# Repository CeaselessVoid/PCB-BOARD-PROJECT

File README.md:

# PCB-BOARD-PROJECT
Currently we still need to flesh out our design in terms of component choice, back up designs and the actual design.
Below is all the data we have currently(the requirements of the project) :
1. Operate up to 4 motors bidirectionally with the pins available to you (listed in the power pinout table). You will need to control 2x brushed DC motors which could each draw 200mA at the highest voltage of a 1S1P battery (the battery is further specified in the battery section).The other 2x motors are for the auxiliary connection and need to operate 500mA each.
2. Place an INA219 for monitoring the battery on the I2C Bus and configure it correctly with respect to the hardware (cannot have BOTH A0 AND A1 on GND)
3. Charge the battery from the 9V input pin (listed in the power pinout table).
4. Have two charging modes for a higher and lower charging current for the battery (200mA, and approximately 600mA ±100mA from the battery perspective.
5. Integrate USB C and get 9V out of the USB Host
6. Provide 2x External Load Switching at 1A each (High Side connected to your 5V)
7. Provide a 3V3 5% accuracy (300mA max) and 5V Out 5% accuracy (1.5A max)
8. Provide an ON/OFF switch. OFF state: battery draw <30uA. ON state: can provide your robot peak current of 2A. The switch needs to shut down 5V and 3V3.

So far we have locked in the components INA219 and possiblely the H-bridge. This will need to be deducted from our budget once we fin a suitable vendor.(As it stands we have $56.5 for the components).
Other points:
1. The board solution should be 82 x 60 (mm)
2. We cannot excede the budget
3. Deadline is the 28th of March (we should try to finalize well before this)
4. All components sourced from JLCPCB

Future things to add here: 
1. We need to add the schemetic and PCB design
2. Possible links to the datasheets we used for an easier time during report writing
3. Any computations we do(again mainly for reference)

https://cdn-shop.adafruit.com/datasheets/ina219.pdf - INA219

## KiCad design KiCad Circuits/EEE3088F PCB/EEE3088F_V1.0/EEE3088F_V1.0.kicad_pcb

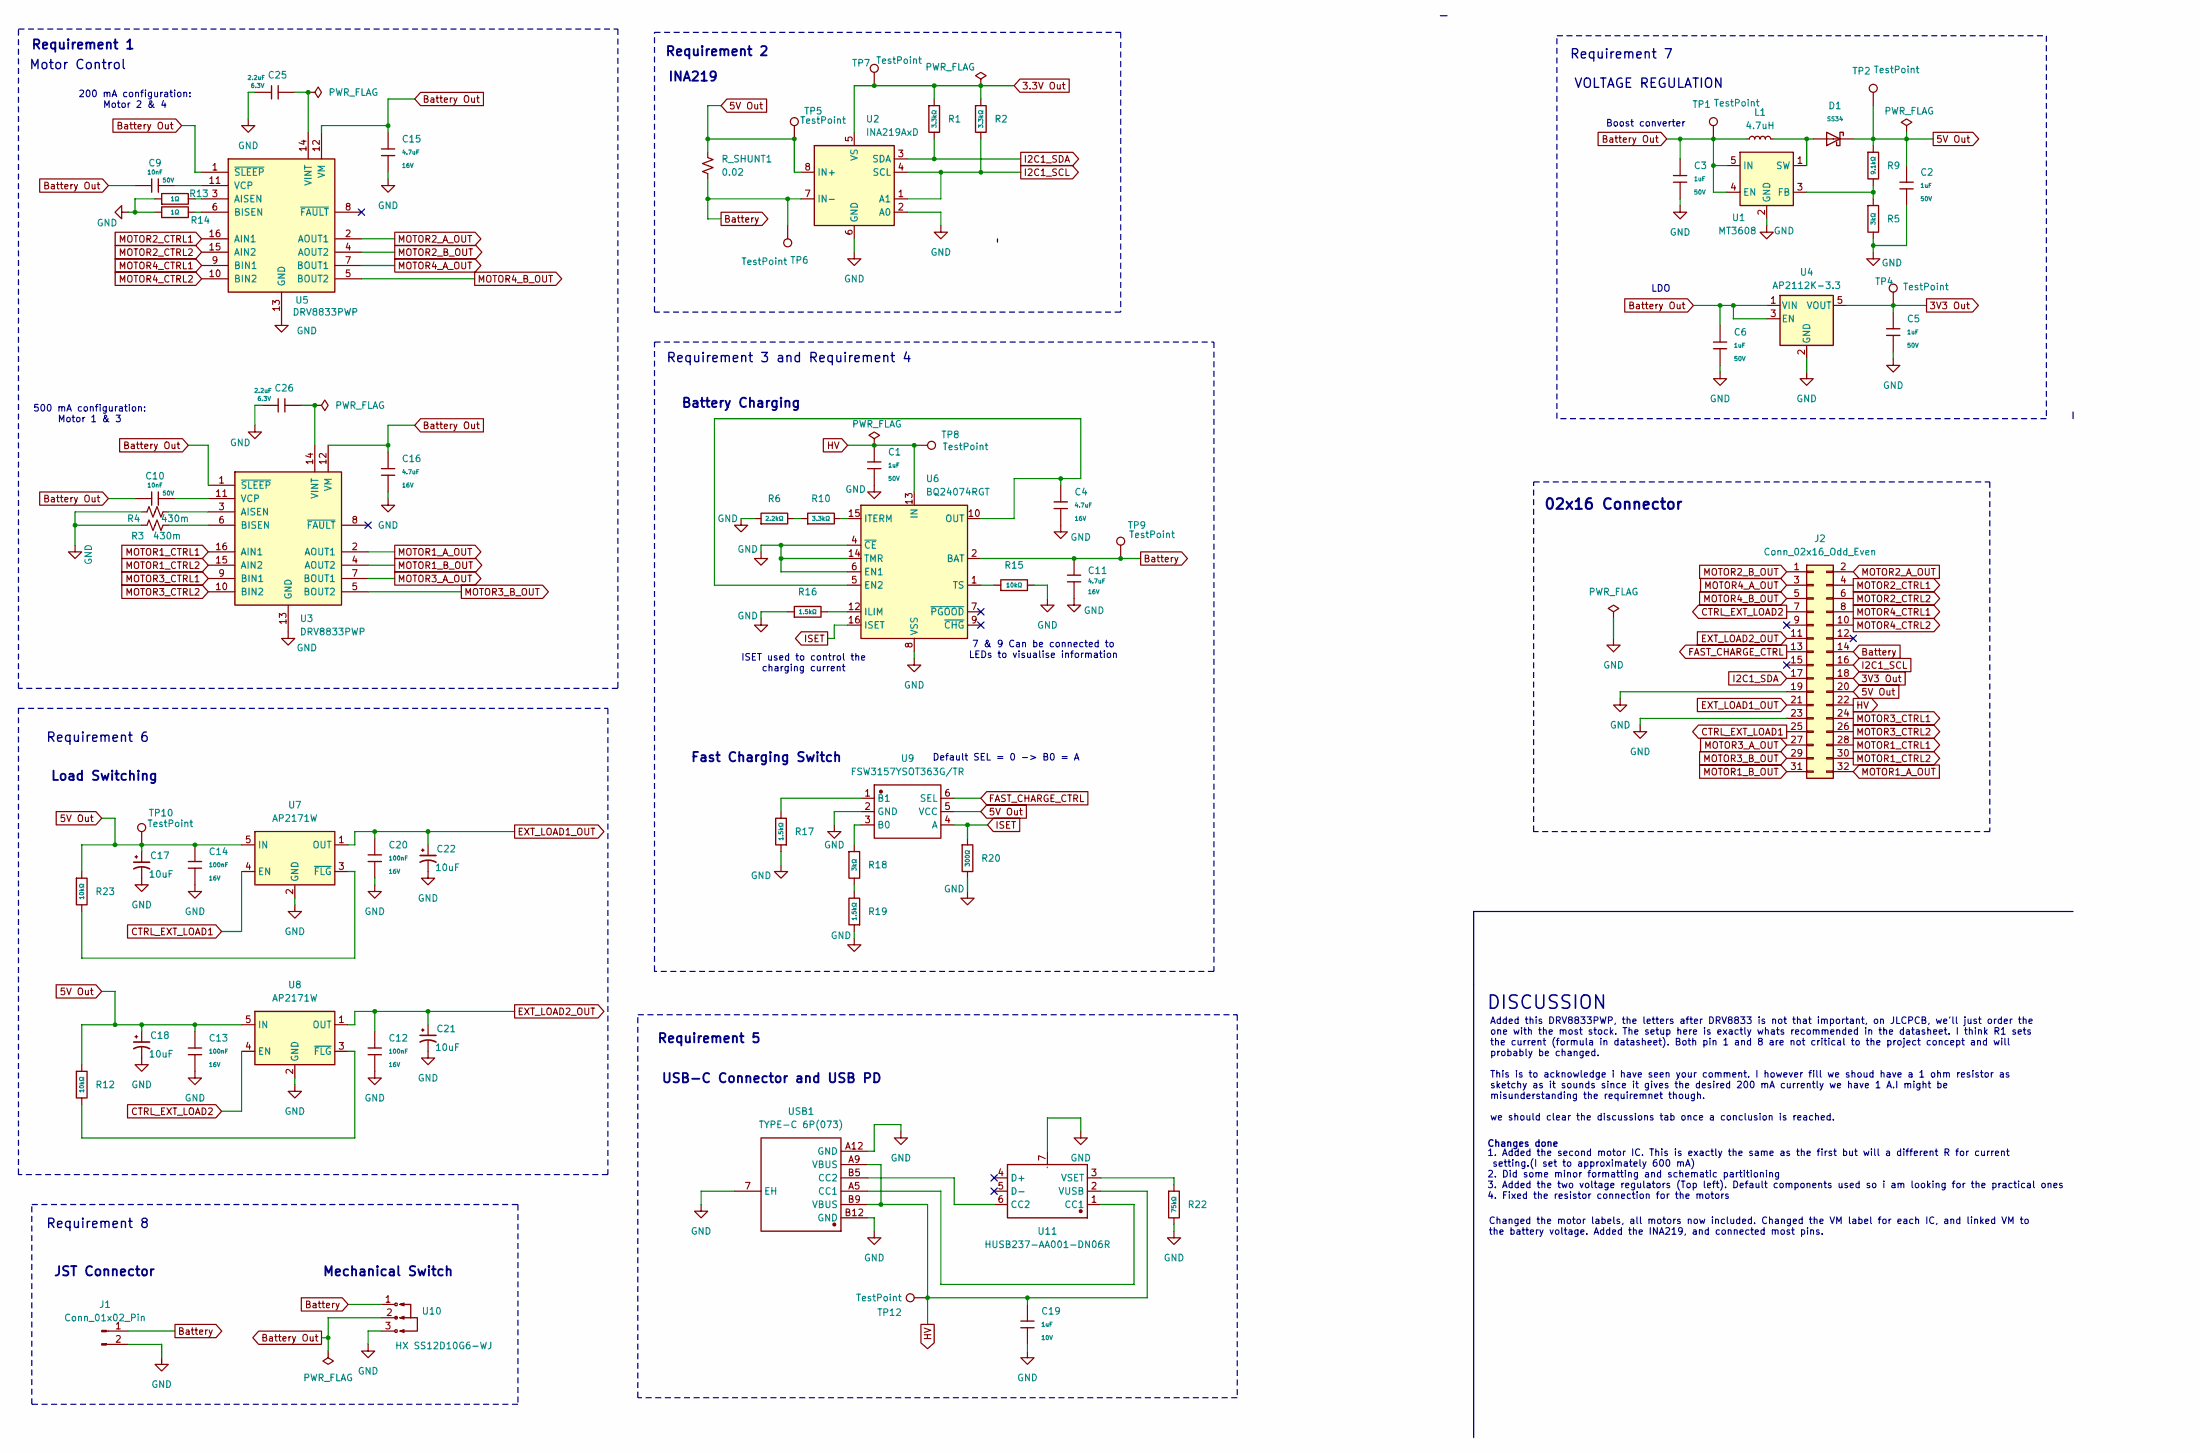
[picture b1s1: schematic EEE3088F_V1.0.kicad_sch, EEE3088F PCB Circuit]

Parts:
C1, C2, C3, C5, C6: 1uF; C_0603; Voltage Rated 50V; Tolerance ±10%; Part CL10A105KB8NNNC; LCSC C15849
C4, C11, C15, C16: 4.7uF; C_0603; Voltage Rated 16V; Tolerance ±10%; Part CL10A475KO8NNNC; LCSC C19666
C9, C10: 10nF; C_0805; Voltage Rated 50V; Tolerance ±10%; Part CL21B103KBANNNC; LCSC C1710
C12, C13, C14, C20: 100nF; C_0402; Voltage Rated 16V; Tolerance ±10%; Part CL05B104KO5NNNC; LCSC C1525
C17, C18, C21, C22: 10uF; CAP-TH_BD5.0-P2.00-D0.8-FD
C19: 1uF; C_0603; Voltage Rated 10V; Tolerance ±10%; Part CL10A105KB8NNNC; LCSC C15849
C25, C26: 2.2uF; C_0402; Voltage Rated 6.3V; Tolerance ±20%; Part CL05A225MQ5NSNC; LCSC C12530
D1: SS34; D_SMA; Forward Voltage (Vf@If) 550mV@3A; Reverse Voltage (Vr) 40V; Part SS34; LCSC C8678
J1: Conn_01x02_Pin; JST_PH_B2B-PH-K_1x02_P2.00mm_Vertical
J2: Conn_02x16_Odd_Even; PinHeader_2x16_P2.54mm_Vertical
L1: 4.7uH; IND-SMD_L2.5-W2.0-VLS252012CX-150M
R1, R2, R10: 3.3kΩ; R_0603; Overload Voltage (Max) 75V; Tolerance ±1%; Part 0603WAF3301T5E; LCSC C22978
R3, R4: 430m; R1206
R5, R18: 3kΩ; R_0603; Overload Voltage (Max) 75V; Tolerance ±1%; Part 0603WAF3001T5E; LCSC C4211
R6: 2.2kΩ; R_0603; Overload Voltage (Max) 75V; Tolerance ±1%; Part 0603WAF2201T5E; LCSC C4190
R9: 9.1kΩ; R_0603; Overload Voltage (Max) 75V; Tolerance ±1%; Part 0603WAF9101T5E; LCSC C23260
R12, R15, R23: 10kΩ; R_0603; Overload Voltage (Max) 75V; Tolerance ±1%; Part 0603WAF1002T5E; LCSC C25804
R13, R14: 1Ω; R_1206; Overload Voltage (Max) 200V; Tolerance ±1%; Part 1206W4F100KT5E; LCSC C17928
R16, R17, R19: 1.5kΩ; R_0603; Overload Voltage (Max) 75V; Tolerance ±1%; Part 0603WAF1501T5E; LCSC C22843
R20: 300Ω; R_0805; Overload Voltage (Max) 150V; Tolerance ±1%; Part 0805W8F3000T5E; LCSC C17617
R22: 75kΩ; R_0603; Overload Voltage (Max) 75V; Tolerance ±1%; Part 0603WAF7502T5E; LCSC C23242
R_SHUNT1: 0.02; R1206
TP1, TP2, TP4, TP5, TP6, TP7, TP8, TP9, TP10, TP12: TestPoint; TestPoint_Pad_4.0x4.0mm
U1: MT3608; SOT-23-5_L3.0-W1.7-P0.95-LS2.8-BR
U2: INA219AxD; SOT-23-8_L3.0-W1.7-P0.65-LS2.8-BR
U3, U5: DRV8833PWP; TSSOP-16_L5.0-W4.4-P0.65-LS6.4-BL-EP
U4: AP2112K-3.3; SOT-25-5_L2.9-W1.6-P0.95-LS2.8-BL
U6: BQ24074RGT; QFN-16_L3.0-W3.0-P0.50-TL-EP1.7
U7, U8: AP2171W; SOT-25-5_L3.0-W1.8-P0.95-LS3.0-BL
U9: FSW3157YSOT363G/TR; SOT-363_L2.1-W1.3-P0.65-LS2.1-BL; Manufacturer Part FSW3157YSOT363G/TR
U10: HX SS12D10G6-WJ; SW-TH_3P-P4.80_HX-SS12D10G6-WJ; Manufacturer Part HX SS12D10G6-WJ
U11: HUSB237-AA001-DN06R; TDFN-6_L2.0-W2.0-P0.65-TL-EP; Manufacturer Part HUSB237-AA001-DN06R
USB1: TYPE-C 6P(073); TYPE-C-SMD_TYPE-C-6P_5; Manufacturer Part TYPE-C 6P(073)

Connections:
3.3V Out: R1.1, R2.1, TP7.1, U2.5 (VS)
3V3 Out: C5.1, J2.18, TP4.1, U4.5 (VOUT)
5V Out: C2.1, C13.1, C14.1, C17.1, C18.1, D1.1, J2.20, R9.1, R12.1, R23.1, R_SHUNT1.1, TP2.1, TP5.1, TP10.1, U2.8 (IN+), U7.5 (IN), U8.5 (IN), U9.5 (VCC)
Battery: C11.1, J1.1, J2.14, R_SHUNT1.2, TP6.1, TP9.1, U2.7 (IN-), U6.2 (BAT), U6.3 (BAT), U10.1
Battery Out: C3.1, C6.1, C9.1, C10.1, C15.1, C16.1, L1.1, TP1.1, U1.4 (EN), U1.5 (IN), U3.1 (~SLEEP), U3.12 (VM), U4.1 (VIN), U4.3 (EN), U5.1 (~SLEEP), U5.12 (VM), U10.2
CTRL_EXT_LOAD1: J2.25, U7.4 (EN)
CTRL_EXT_LOAD2: J2.7, U8.4 (EN)
EXT_LOAD1_OUT: C20.1, C22.1, J2.21, U7.1 (OUT)
EXT_LOAD2_OUT: C12.1, C21.1, J2.11, U8.1 (OUT)
FAST_CHARGE_CTRL: J2.13, U9.6 (SEL)
GND: C1.2, C2.2, C3.2, C4.2, C5.2, C6.2, C11.2, C12.2, C13.2, C14.2, C15.2, C16.2, C17.2, C18.2, C19.2, C20.2, C21.2, C22.2, C25.1, C26.1, J1.2, J2.19, J2.23, R3.1, R4.1, R5.2, R6.1, R13.1, R14.1, R15.2, R16.1, R17.1, R19.1, R20.2, R22.2, U1.2 (GND), U2.2 (A0), U2.6 (GND), U3.13 (GND), U3.17 (GND), U4.2 (GND), U5.13 (GND), U5.17 (GND), U6.4 (~CE), U6.6 (EN1), U6.8 (VSS), U6.14 (TMR), U6.17 (VSS), U7.2 (GND), U8.2 (GND), U9.2 (GND), U10.3, U11.7 (GND), USB1.7 (EH), USB1.A12 (GND), USB1.B12 (GND)
HV: C1.1, C19.1, J2.22, TP8.1, TP12.1, U6.13 (IN), U11.2 (VUSB), USB1.A9 (VBUS), USB1.B9 (VBUS)
I2C1_SCL: J2.16, R2.2, U2.1 (A1), U2.4 (SCL)
I2C1_SDA: J2.17, R1.2, U2.3 (SDA)
ISET: R20.1, U6.16 (ISET), U9.4 (A)
MOTOR1_A_OUT: J2.32, U3.2 (AOUT1)
MOTOR1_B_OUT: J2.31, U3.4 (AOUT2)
MOTOR1_CTRL1: J2.28, U3.16 (AIN1)
MOTOR1_CTRL2: J2.30, U3.15 (AIN2)
MOTOR2_A_OUT: J2.2, U5.2 (AOUT1)
MOTOR2_B_OUT: J2.1, U5.4 (AOUT2)
MOTOR2_CTRL1: J2.4, U5.16 (AIN1)
MOTOR2_CTRL2: J2.6, U5.15 (AIN2)
MOTOR3_A_OUT: J2.27, U3.7 (BOUT1)
MOTOR3_B_OUT: J2.29, U3.5 (BOUT2)
MOTOR3_CTRL1: J2.24, U3.9 (BIN1)
MOTOR3_CTRL2: J2.26, U3.10 (BIN2)
MOTOR4_A_OUT: J2.3, U5.7 (BOUT1)
MOTOR4_B_OUT: J2.5, U5.5 (BOUT2)
MOTOR4_CTRL1: J2.8, U5.9 (BIN1)
MOTOR4_CTRL2: J2.10, U5.10 (BIN2)
unnamed: R6.2, R10.1
unnamed: R18.2, R19.2
unnamed: R5.1, R9.2, U1.3 (FB)
unnamed: D1.2, L1.2, U1.1 (SW)
unnamed: R4.2, U3.3 (AISEN)
unnamed: R3.2, U3.6 (BISEN)
unnamed: C10.2, U3.11 (VCP)
unnamed: C26.2, U3.14 (VINT)
unnamed: R13.2, U5.3 (AISEN)
unnamed: R14.2, U5.6 (BISEN)
unnamed: C9.2, U5.11 (VCP)
unnamed: C25.2, U5.14 (VINT)
unnamed: C4.1, U6.5 (EN2), U6.10 (OUT), U6.11 (OUT)
unnamed: R16.2, U6.12 (ILIM)
unnamed: R10.2, U6.15 (ITERM)
unnamed: R15.1, U6.1 (TS)
unnamed: R23.2, U7.3 (~FLG)
unnamed: R12.2, U8.3 (~FLG)
unnamed: R18.1, U9.3 (B0)
unnamed: R17.2, U9.1 (B1)
unnamed: U11.1 (CC1), USB1.A5 (CC1)
unnamed: U11.6 (CC2), USB1.B5 (CC2)
unnamed: R22.1, U11.3 (VSET)

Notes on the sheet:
Default SEL = 0 -> B0 = A
JST Connector
Battery Charging
Mechanical Switch
Requirement 5
INA219
ISET used to control the charging current
200 mA configuration: Motor 2 & 4
VOLTAGE REGULATION
Requirement 2
LDO
02x16 Connector
Added this DRV8833PWP, the letters after DRV8833 is not that important, on JLCPCB, we'll just order the one with the most stock. The setup here is exactly whats recommended in the datasheet. I think R1 sets the current (formula in datasheet). Both pin 1 and 8 are not critical to the project concept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
Requirement 1
USB-C Connector and USB PD
Requirement 3 and Requirement 4
Requirement 8
DISCUSSION
1. Added the second motor IC. This is exactly the same as the first but will a different R for current setting.(I set to approximately 600 mA) 2. Did some minor formatting and schematic partitioning 3. Added the two voltage regulators (Top left). Default components used so i am looking for the prac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
Changes done
Motor Control
Load Switching
500 mA configuration: Motor 1 & 3
Requirement 7
7 & 9 Can be connected to LEDs to visualise information
Fast Charging Switch
Changed the motor labels, all motors now included. Changed the VM label for each IC, and linked VM to the battery voltage. Added the INA219, and connected most pins.
Requirement 6
Boost converter

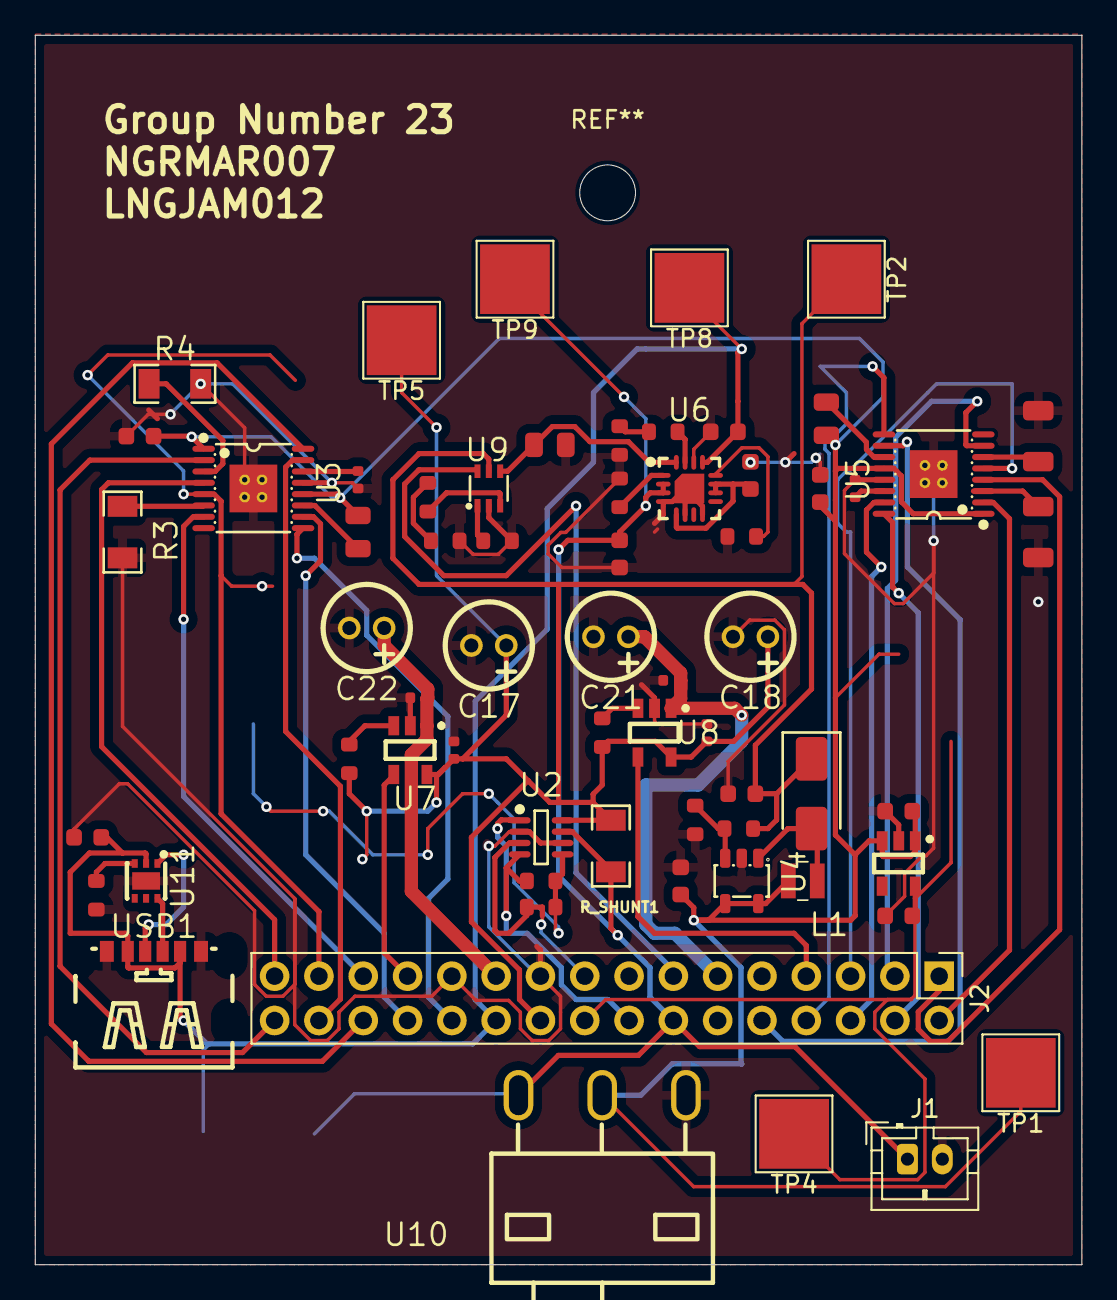
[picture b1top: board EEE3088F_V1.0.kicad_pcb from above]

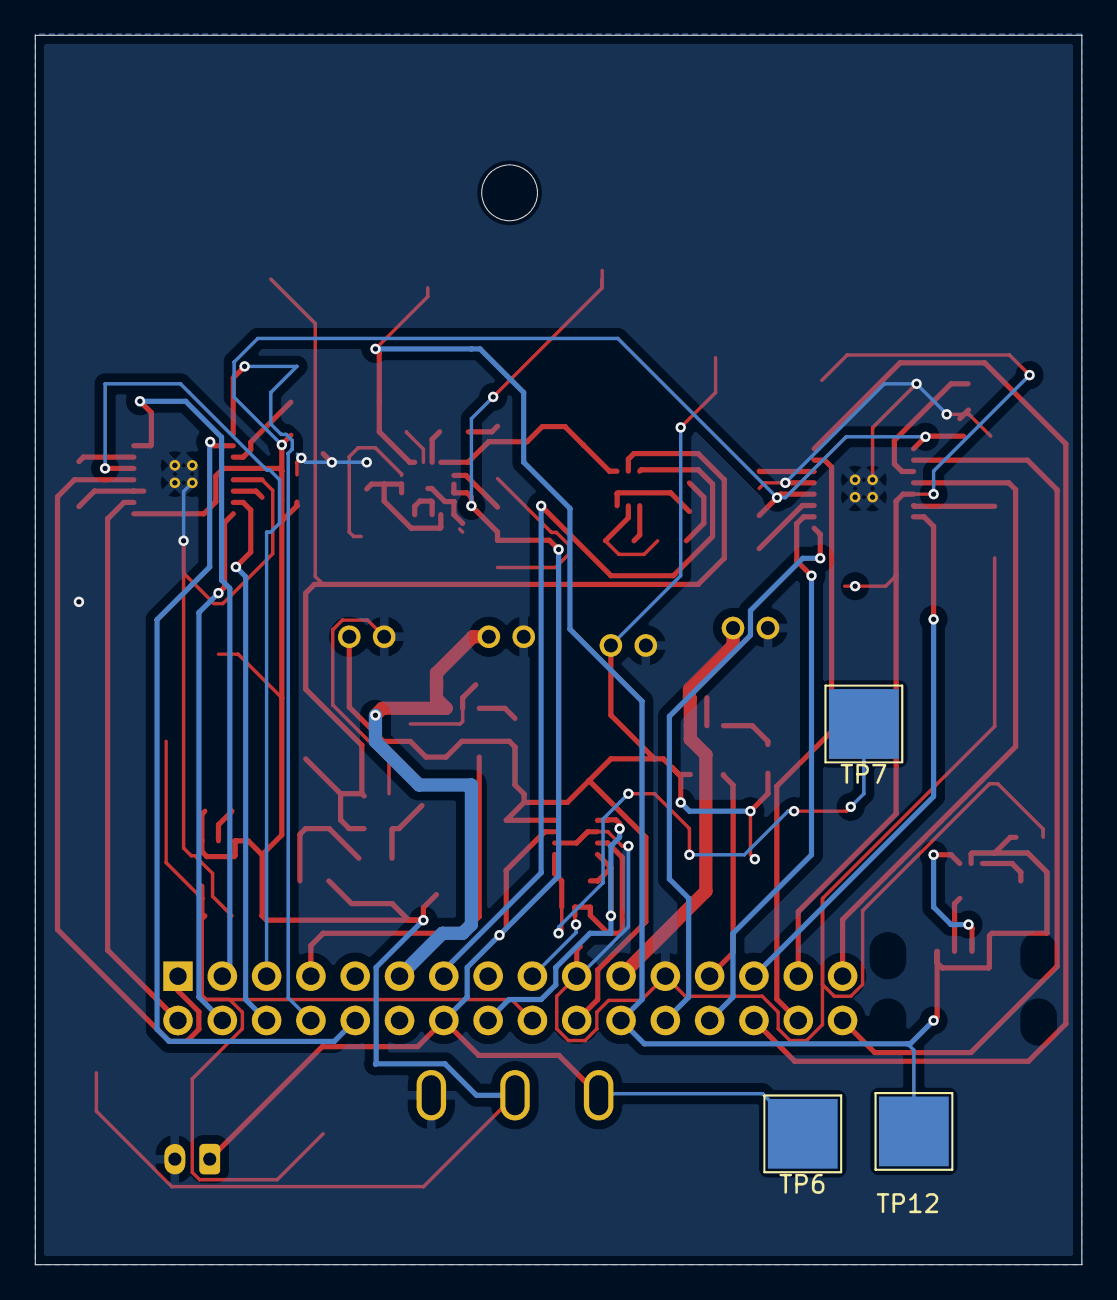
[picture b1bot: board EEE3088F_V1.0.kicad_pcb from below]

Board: 2 copper layers, 60.0 x 70.5 mm, 67 parts (3 on the bottom side), 54 nets.

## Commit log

2025-03-19 Create README.md
    For your reference
2025-03-21 Create DESIGN AND COMPONENTS.md
    This will purely have discussions.
2025-03-22 Block Diagrams for power module
    Helpful for understanding and pin outs
2025-03-22 More organisation
2025-03-23 Added Kicad circuit (Blank so far)
2025-03-24 2x16 connector added
2025-03-24 Added 1 H-bridge (DRV8833PWP)
2025-03-25 Added H-bridge and voltage regulators
2025-03-25 Added INA219 and did housekeeping
2025-03-26 Updated to v1.1
2025-03-26 Added Battery Charger
2025-03-26 Minor label added
2025-03-26 Added Load switching circuit and reorganised the page
2025-03-26 added INA219
2025-03-26 added footprints folder
2025-03-27 Analogue Switch added
2025-03-27 Added Mechanical Switch
2025-03-27 added symbols
2025-03-27 Increased page size and added footprint to imported components
2025-03-27 bigger page, added USB stuff
2025-03-27 Footprints added
2025-03-27 Done :)
2025-03-27 PCB added
2025-03-27 Updated components, started PCB
2025-03-27 Pcb changes
2025-03-27 Went untracked for some reason
2025-03-27 Updated the Kicad pcb
2025-03-27 Component position complete
2025-03-27 Minor edits
2025-03-27 PCB connected but not error free
2025-03-28 Edited Kicad
2025-03-28 Updated pcb (missing connections)
2025-03-28 Changes in pcb
2025-03-28 Fixed pcb
2025-03-28 Updated PCB
2025-03-28 added test points
2025-03-28 Final PCB
